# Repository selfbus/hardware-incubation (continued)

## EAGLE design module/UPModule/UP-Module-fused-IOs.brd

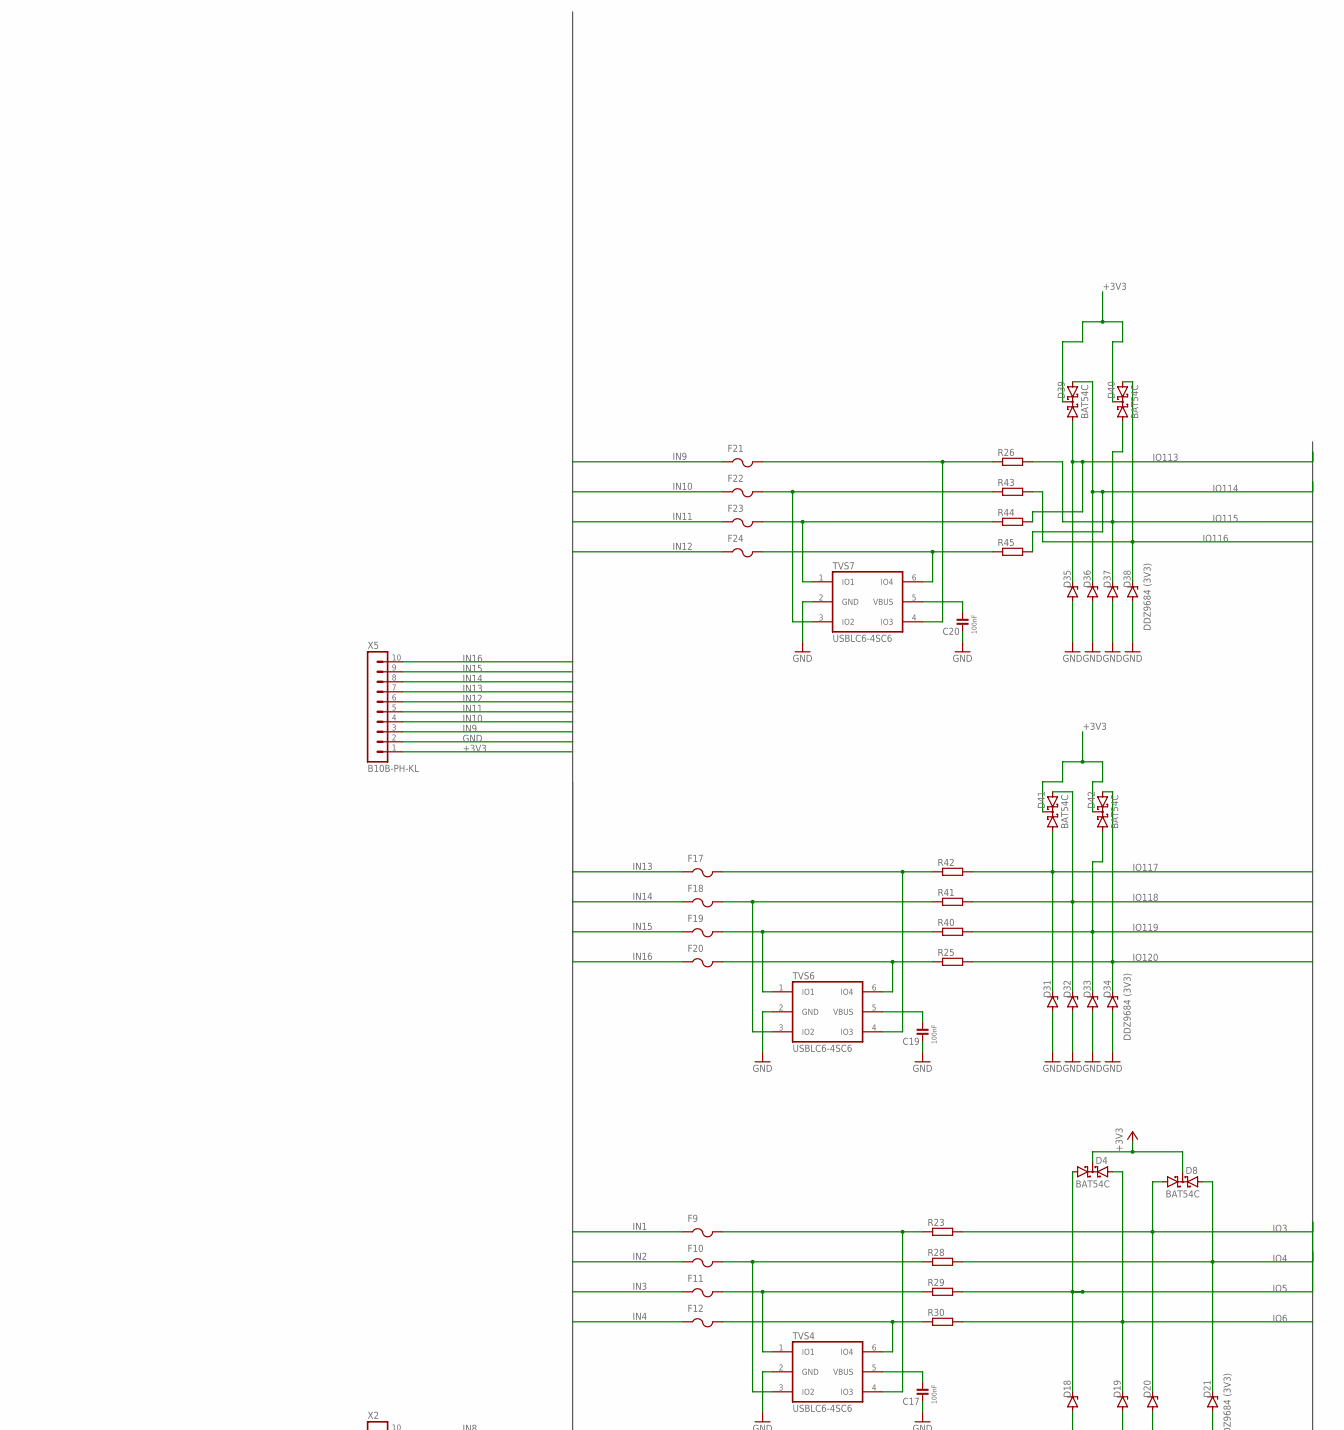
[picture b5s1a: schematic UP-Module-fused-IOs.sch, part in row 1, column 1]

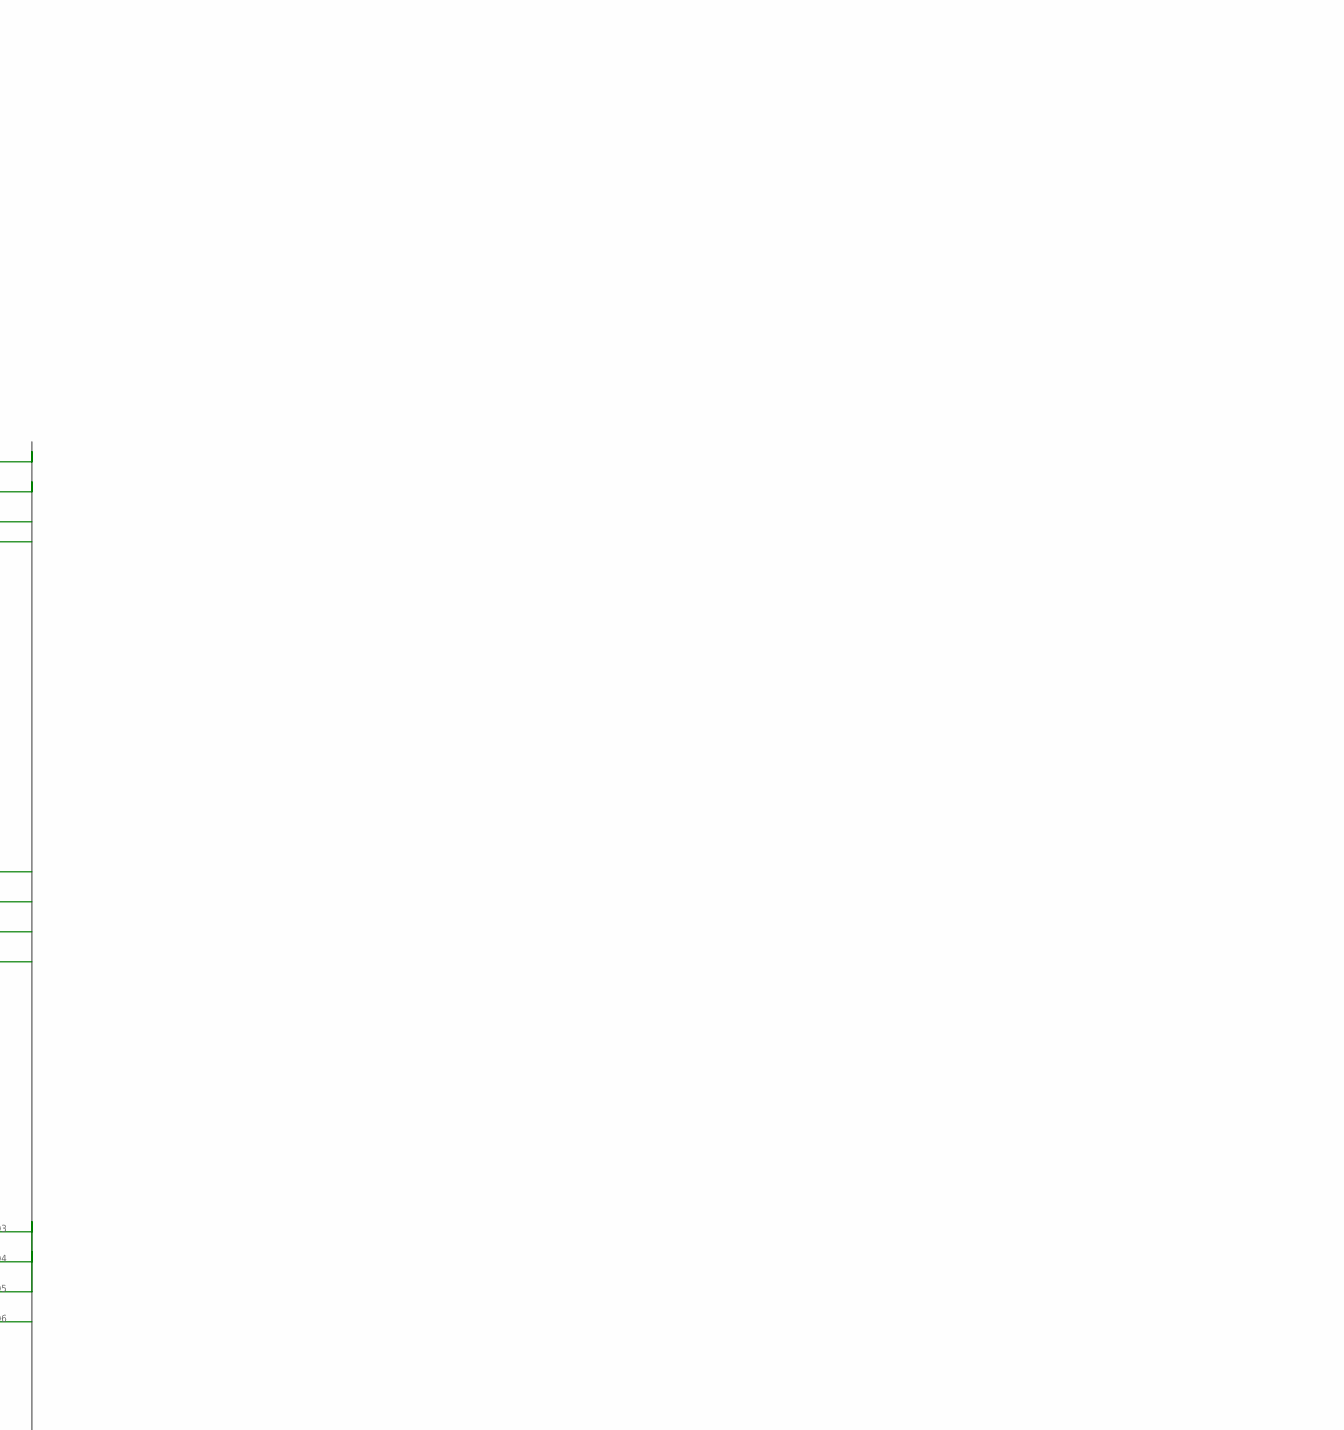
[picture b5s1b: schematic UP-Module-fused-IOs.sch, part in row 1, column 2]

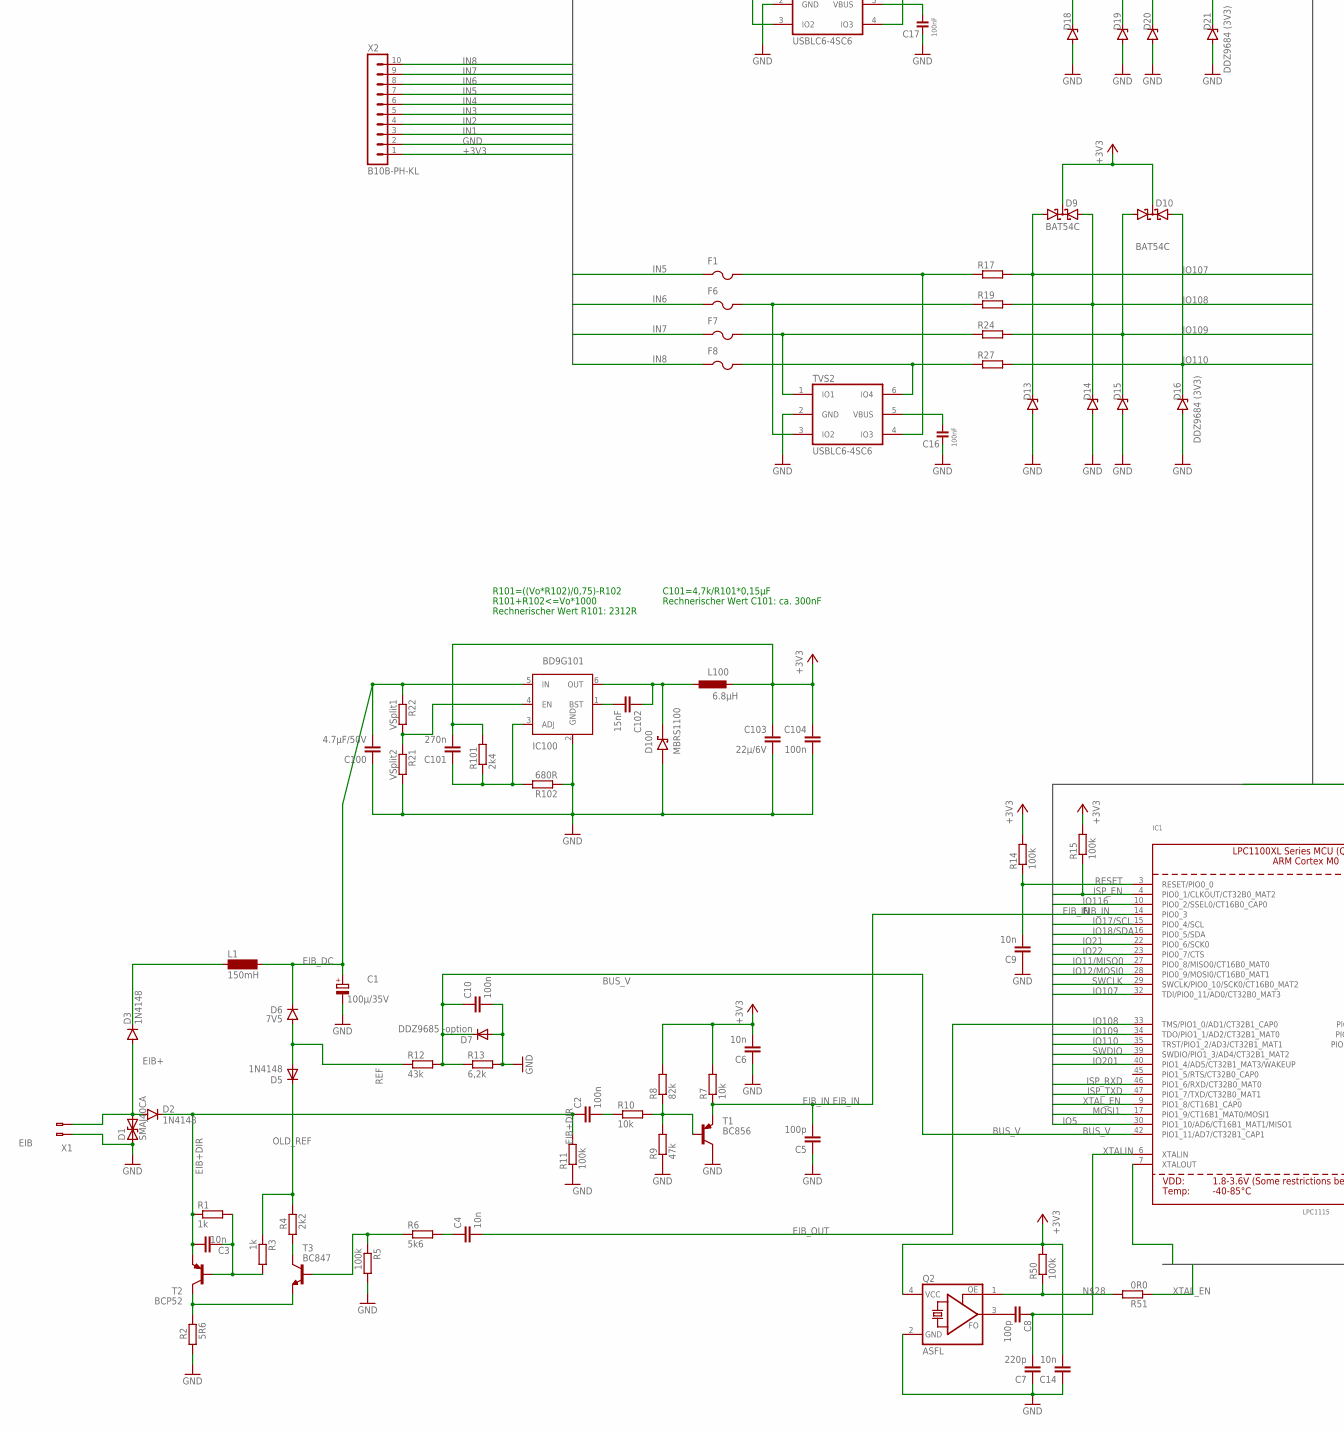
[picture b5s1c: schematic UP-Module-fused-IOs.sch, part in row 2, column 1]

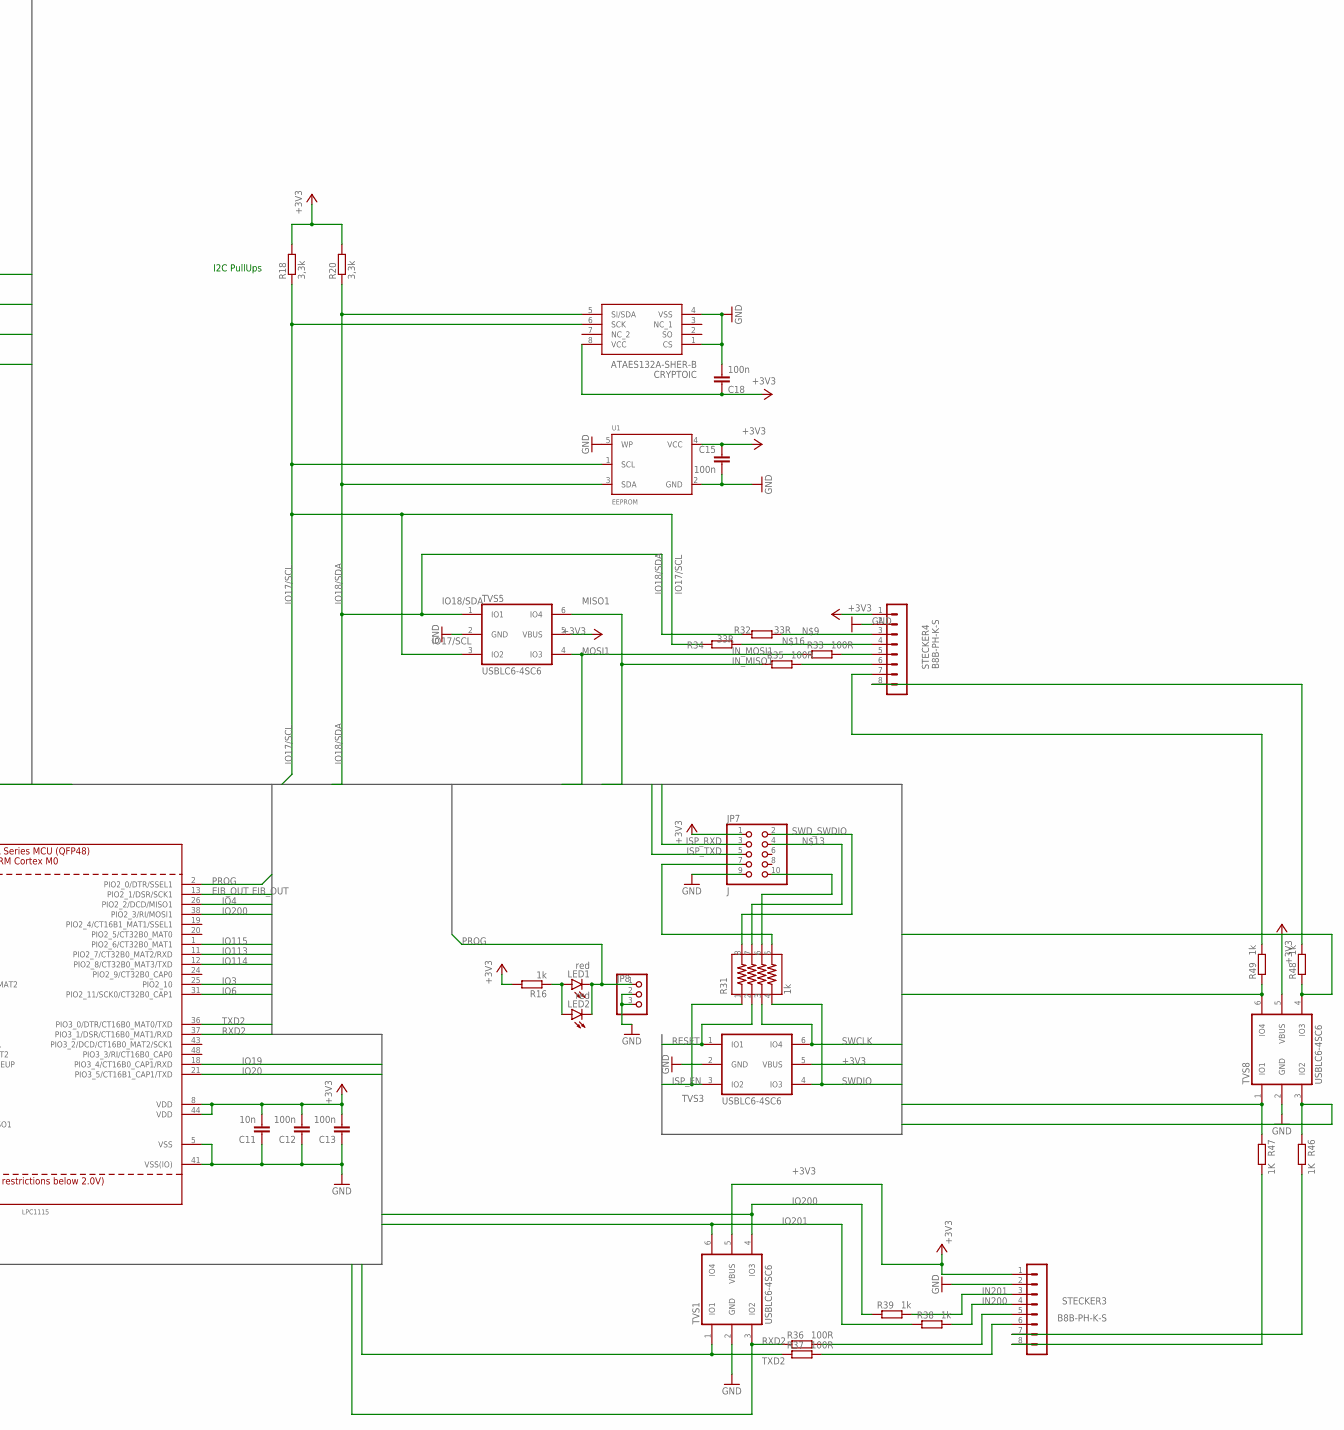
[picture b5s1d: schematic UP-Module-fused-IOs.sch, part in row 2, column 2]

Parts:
C1: 100µ/35V; SANYO-OSCON_SMD_C6
C2, C10, C12, C13, C15, C18, C104: 100n; C0805
C3, C4, C6, C9, C11, C14: 10n; C0805
C5, C8: 100p; C0805
C7: 220p; C0805
C16, C17, C19, C20: 100nF; C0805
C100: 4.7µF/50V; C0805
C101: 270n; C0805
C102: 15nF; C0805
C103: 22µ/6V; C0805
CRYPTOIC: ATAES132A-SHER-B; SOIC127P600X175-8N
D1: SMAJ40CA; DO214AC
D2, D3, D5: 1N4148; SOD323-R
D4, D8, D9, D10, D39, D40, D41, D42: BAT54C; SOT23
D6: 7V5; SOD323-R
D7: DDZ9685 -option; SOD-123
D13, D14, D15, D16, D18, D19, D20, D21, D31, D32, D33, D34, D35, D36, D37, D38: DDZ9684 (3V3); SODFL3718X115
D100: MBRS1100; SOD123FL
F1, F6, F7, F8, F9, F10, F11, F12, F17, F18, F19, F20, F21, F22, F23, F24: PTCFUSE-0805; F0805
IC1: LPC1115; LQFP48
IC100: BD9G101; SOT23-6
JP7: J; 2X05M
JP8: PINHD-1X3; 1X03
L1: 150mH; BS11
L100: 6.8µH; L4532P
LED1: red; CHIPLED_1206
LED2: red; LED3MM
Q2: ASFL; ASF
R1, R3, R16, R38, R39, R48, R49: 1k; R0805
R2: 5R6; R0805
R4: 2k2; R0805
R5, R11, R14, R15, R50: 100k; R0805
R6: 5k6; R0805
R7, R10: 10k; R0805
R8: 82k; R0805
R9: 47k; R0805
R12: 43k; R0805
R13: 6,2k; R0805
R17, R19, R23, R24, R25, R26, R27, R28, R29, R30, R40, R41, R42, R43, R44, R45: R-EU_R0805; R0805
R18, R20: 3,3k; R0805
R21: VSplit2; R0805
R22: VSplit1; R0805
R31: 1k; YC164-JR-0733RL
R32, R34: 33R; R0805
R33, R35, R36, R37: 100R; R0805
R46, R47: 1K; R0805
R51: 0R0; R0805
R101: 2k4; R0805
R102: 680R; R0805
STECKER3, STECKER4: B8B-PH-K-S
T1: BC856; SOT23-BEC
T2: BCP52; SOT223
T3: BC847; SOT23
TVS1, TVS2, TVS3, TVS4, TVS5, TVS6, TVS7, TVS8: USBLC6-4SC6; SOT-23-6L
U1: EEPROM; SOT23-5
X1: EIB; BUSKLEMME243-724
X2, X5: B10B-PH-KL; B10B-PH-K-S

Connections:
+3V3: C6.2, C11.2, C12.2, C13.2, C14.2, C15.1, C18.1, C101.2, C103.1, C104.1, CRYPTOIC.8 (VCC), D4.3 (CC), D8.3 (CC), D9.3 (CC), D10.3 (CC), D39.3 (CC), D40.3 (CC), D41.3 (CC), D42.3 (CC), IC1.8 (VDD), IC1.44 (VDD), JP7.1, L100.2, Q2.4 (VCC), R7.2, R8.2, R14.2, R15.2, R16.2, R18.2, R20.2, R50.2, R101.2, STECKER3.1, STECKER4.1, TVS1.5 (VBUS), TVS3.5 (VBUS), TVS5.5 (VBUS), TVS8.5 (VBUS), U1.4 (VCC), X2.1, X5.1
BST: C102.2, IC100.1 (BST)
BUS_V: C10.2, D7.C, IC1.42 (PIO1_11/AD7/CT32B1_CAP1), R12.2, R13.1
EIB+: D1.C (2), D2.A, D3.A, X1.2 (B-2)
EIB+DIR: C2.1, C3.1, D2.C, R1.1, R11.2, T2.3 (E)
EIB_DC: C1.+, C100.2, D6.C, IC100.5 (IN), L1.2, R22.1
EIB_IN: C5.2, IC1.14 (PIO0_3), R7.1, T1.E
EIB_OUT: C4.2, IC1.13 (PIO2_1/DSR/SCK1)
FB: C101.1, IC100.3 (ADJ), R101.1, R102.2
GND: C1.-, C5.1, C6.1, C7.1, C9.1, C10.1, C11.1, C12.1, C13.1, C14.1, C15.2, C16.1, C17.1, C18.2, C19.1, C20.1, C100.1, C103.2, C104.2, CRYPTOIC.1 (CS), CRYPTOIC.4 (VSS), D1.A (1), D7.A, D13.2 (A), D14.2 (A), D15.2 (A), D16.2 (A), D18.2 (A), D19.2 (A), D20.2 (A), D21.2 (A), D31.2 (A), D32.2 (A), D33.2 (A), D34.2 (A), D35.2 (A), D36.2 (A), D37.2 (A), D38.2 (A), D100.A, IC1.5 (VSS), IC1.41 (VSS(IO)), IC100.2 (GND), JP7.9, JP8.2, JP8.3, Q2.2 (GND), R2.1, R5.2, R9.1, R11.1, R13.2, R21.2, R102.1, STECKER3.2, STECKER4.2, T1.C, TVS1.2 (GND), TVS2.2 (GND), TVS3.2 (GND), TVS4.2 (GND), TVS5.2 (GND), TVS6.2 (GND), TVS7.2 (GND), TVS8.2 (GND), U1.2 (GND), U1.5 (WP), X1.1 (B-1), X2.2, X5.2
IN1: F9.1, X2.3
IN2: F10.1, X2.4
IN3: F11.1, X2.5
IN4: F12.1, X2.6
IN5: F1.1, X2.7
IN6: F6.1, X2.8
IN7: F7.1, X2.9
IN8: F8.1, X2.10
IN9: F21.1, X5.3
IN10: F22.1, X5.4
IN11: F23.1, X5.5
IN12: F24.1, X5.6
IN13: F17.1, X5.7
IN14: F18.1, X5.8
IN15: F19.1, X5.9
IN16: F20.1, X5.10
IN200: R38.2, STECKER3.4
IN201: R39.2, STECKER3.3
IN_MISO1: R35.2, STECKER4.6
IN_MOSI1: R33.2, STECKER4.5
IO3: D8.1 (A1), D20.1 (C), IC1.25 (PIO2_10), R23.2
IO4: D8.2 (A2), D21.1 (C), IC1.26 (PIO2_2/DCD/MISO1), R28.2
IO5: D4.1 (A1), D18.1 (C), IC1.30 (PIO1_10/AD6/CT16B1_MAT1/MISO1), R29.2
IO6: D4.2 (A2), D19.1 (C), IC1.31 (PIO2_11/SCK0/CT32B0_CAP1), R30.2
IO11/MISO0: IC1.27 (PIO0_8/MISO0/CT16B0_MAT0)
IO12/MOSI0: IC1.28 (PIO0_9/MOSI0/CT16B0_MAT1)
IO17/SCL: CRYPTOIC.6 (SCK), IC1.15 (PIO0_4/SCL), R18.1, R34.1, TVS5.3 (IO2), U1.1 (SCL)
IO18/SDA: CRYPTOIC.5 (SI/SDA), IC1.16 (PIO0_5/SDA), R20.1, R32.1, TVS5.1 (IO1), U1.3 (SDA)
IO19: IC1.18 (PIO3_4/CT16B0_CAP1/RXD), R47.1, TVS8.1 (IO1)
IO20: IC1.21 (PIO3_5/CT16B1_CAP1/TXD), R46.1, TVS8.3 (IO2)
IO21: IC1.22 (PIO0_6/SCK0), R49.1, TVS8.6 (IO4)
IO22: IC1.23 (PIO0_7/CTS), R48.1, TVS8.4 (IO3)
IO107: D9.1 (A1), D13.1 (C), IC1.32 (TDI/PIO0_11/AD0/CT32B0_MAT3), R17.2
IO108: D9.2 (A2), D14.1 (C), IC1.33 (TMS/PIO1_0/AD1/CT32B1_CAP0), R19.2
IO109: D10.1 (A1), D15.1 (C), IC1.34 (TDO/PIO1_1/AD2/CT32B1_MAT0), R24.2
IO110: D10.2 (A2), D16.1 (C), IC1.35 (TRST/PIO1_2/AD3/CT32B1_MAT1), R27.2
IO113: D35.1 (C), D39.1 (A1), IC1.11 (PIO2_7/CT32B0_MAT2/RXD), R44.2
IO114: D36.1 (C), D39.2 (A2), IC1.12 (PIO2_8/CT32B0_MAT3/TXD), R45.2
IO115: D37.1 (C), D40.1 (A1), IC1.1 (PIO2_6/CT32B0_MAT1), R26.2
IO116: D38.1 (C), D40.2 (A2), IC1.10 (PIO0_2/SSEL0/CT16B0_CAP0), R43.2
IO117: D31.1 (C), D41.1 (A1), R42.2
IO118: D32.1 (C), D41.2 (A2), R41.2
IO119: D33.1 (C), D42.1 (A1), R40.2
IO120: D34.1 (C), D42.2 (A2), R25.2
IO200: IC1.38 (PIO2_3/RI/MOSI1), R39.1, TVS1.4 (IO3)
IO201: IC1.40 (PIO1_4/AD5/CT32B1_MAT3/WAKEUP), R38.1, TVS1.6 (IO4)
ISP_EN: IC1.4 (PIO0_1/CLKOUT/CT32B0_MAT2), R15.1, R31.1, TVS3.3 (IO2)
ISP_RXD: IC1.46 (PIO1_6/RXD/CT32B0_MAT0), JP7.3
ISP_TXD: IC1.47 (PIO1_7/TXD/CT32B0_MAT1), JP7.5
LX: C102.1, D100.C, IC100.6 (OUT), L100.1
MISO1: R35.1, TVS5.6 (IO4)
MOSI1: IC1.17 (PIO1_9/CT16B1_MAT0/MOSI1), R33.1, TVS5.4 (IO3)
unnamed: C2.2, R10.1
unnamed: D3.C, L1.1
unnamed: C4.1, R6.2
unnamed: IC100.4 (EN), R21.1, R22.2
unnamed: R4.1, T3.3 (C)
unnamed: R2.2, T2.2 (C), T2.4 (C), T3.2 (E)
unnamed: JP7.7, R31.5
unnamed: R32.2, STECKER4.3
unnamed: C8.2, Q2.3 (FO)
unnamed: JP7.10, R31.6
unnamed: R5.1, R6.1, T3.1 (B)
unnamed: JP7.4, R31.7
unnamed: R8.1, R9.2, R10.2, T1.B
unnamed: C3.2, R1.2, R3.2, T2.1 (B)
unnamed: R34.2, STECKER4.4
unnamed: F1.2, R17.1, TVS2.4 (IO3)
unnamed: F6.2, R19.1, TVS2.3 (IO2)
unnamed: F7.2, R24.1, TVS2.1 (IO1)
unnamed: F8.2, R27.1, TVS2.6 (IO4)
unnamed: C16.2, TVS2.5 (VBUS)
unnamed: F10.2, R28.1, TVS4.3 (IO2)
unnamed: F12.2, R30.1, TVS4.6 (IO4)
unnamed: C17.2, TVS4.5 (VBUS)
unnamed: F11.2, R29.1, TVS4.1 (IO1)
unnamed: F9.2, R23.1, TVS4.4 (IO3)
unnamed: Q2.1 (OE), R50.1, R51.2
unnamed: R36.2, STECKER3.5
unnamed: R37.2, STECKER3.6
unnamed: F18.2, R41.1, TVS6.3 (IO2)
unnamed: F20.2, R25.1, TVS6.6 (IO4)
unnamed: C19.2, TVS6.5 (VBUS)
unnamed: F19.2, R40.1, TVS6.1 (IO1)
unnamed: F17.2, R42.1, TVS6.4 (IO3)
unnamed: F22.2, R43.1, TVS7.3 (IO2)
unnamed: F24.2, R45.1, TVS7.6 (IO4)
unnamed: C20.2, TVS7.5 (VBUS)
unnamed: LED1.A, LED2.A, R16.1
unnamed: F23.2, R44.1, TVS7.1 (IO1)
unnamed: F21.2, R26.1, TVS7.4 (IO3)
unnamed: R47.2, STECKER3.8
unnamed: R46.2, STECKER3.7
unnamed: R49.2, STECKER4.7
unnamed: R48.2, STECKER4.8
OLD_REF: D5.C, R3.1, R4.2
PROG: IC1.2 (PIO2_0/DTR/SSEL1), JP8.1, LED1.C, LED2.K (C)
REF: D5.A, D6.A, R12.1
RESET: C9.2, IC1.3 (RESET/PIO0_0), R14.1, R31.2, TVS3.1 (IO1)
RXD2: IC1.37 (PIO3_1/DSR/CT16B0_MAT1/RXD), R36.1, TVS1.3 (IO2)
SWCLK: IC1.29 (SWCLK/PIO0_10/SCK0/CT16B0_MAT2), R31.3, TVS3.6 (IO4)
SWDIO: IC1.39 (SWDIO/PIO1_3/AD4/CT32B1_MAT2), R31.4, TVS3.4 (IO3)
SWD_SWDIO: JP7.2, R31.8
TXD2: IC1.36 (PIO3_0/DTR/CT16B0_MAT0/TXD), R37.1, TVS1.1 (IO1)
XTALIN: C7.2, C8.1, IC1.6 (XTALIN)
XTALOUT: IC1.7 (XTALOUT)
XTAL_EN: IC1.9 (PIO1_8/CT16B1_CAP0), R51.1

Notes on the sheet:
R101=((Vo*R102)/0,75)-R102
R101+R102<=Vo*1000
Rechnerischer Wert R101: 2312R
C101=4,7k/R101*0,15µF
Rechnerischer Wert C101: ca. 300nF
I2C PullUps

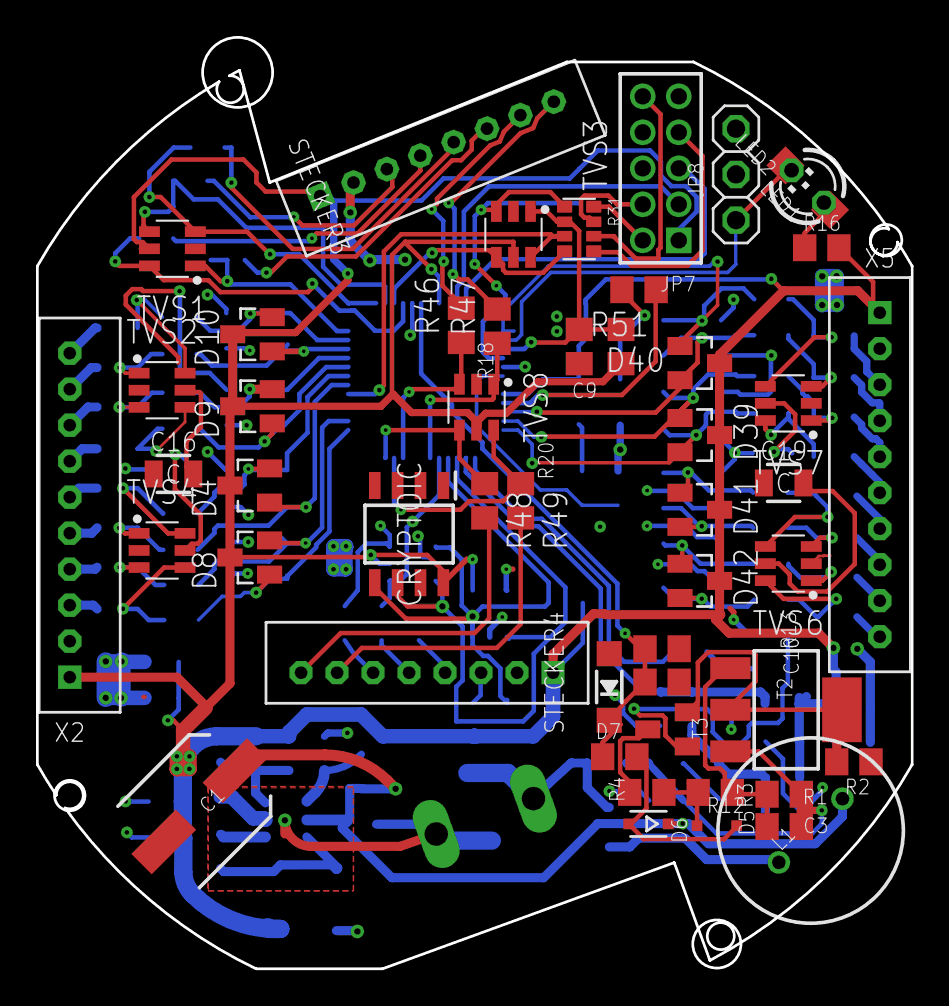
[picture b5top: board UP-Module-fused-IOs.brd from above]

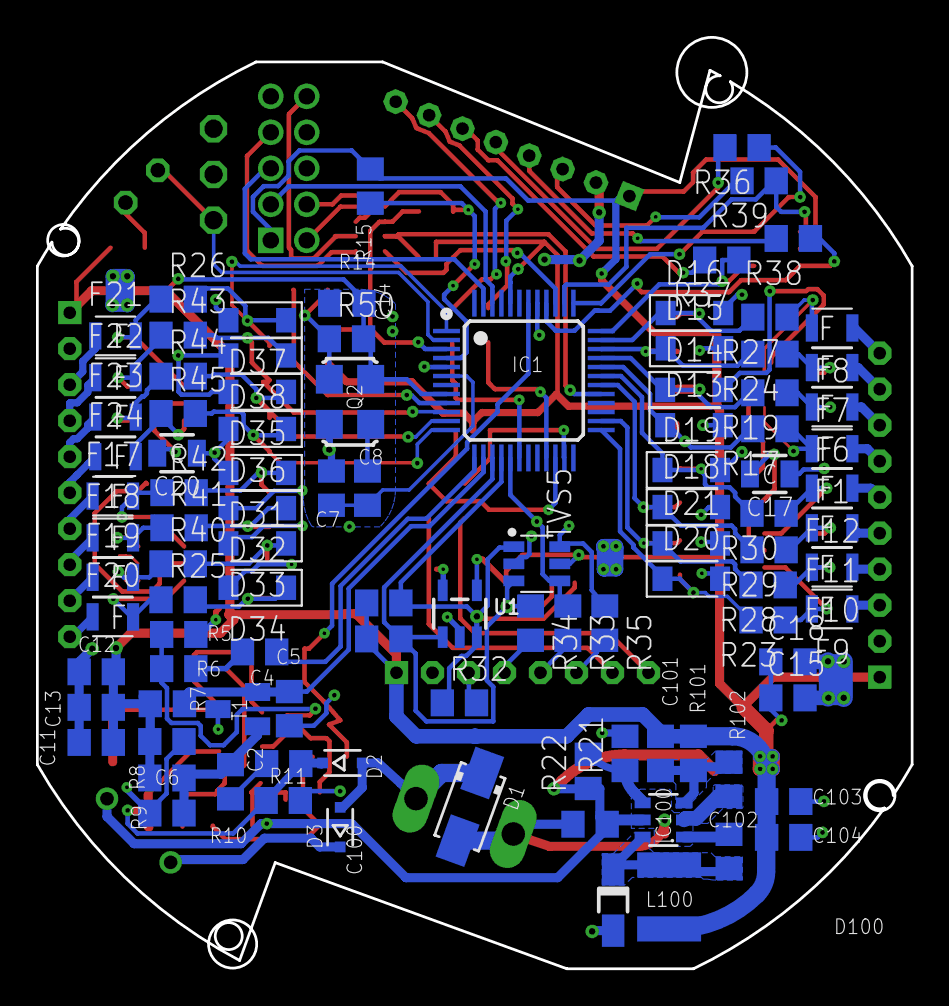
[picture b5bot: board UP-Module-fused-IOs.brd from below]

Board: 2 copper layers, 48.6 x 51.7 mm, 152 parts (101 on the bottom side), 114 nets.

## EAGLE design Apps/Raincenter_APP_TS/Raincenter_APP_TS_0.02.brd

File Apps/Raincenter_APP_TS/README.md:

# Raincenter_APP_TS

KNX-Modul für das Hauswasserwerk ESPA-Tacomat bzw. Raincenter Comfort 15
KNX-module for the domestic waterworks ESPA-Tacomat or Raincenter Comfort 15

[Firmware: raincenter-bim112](https://github.com/selfbus/software-arm-incubation/tree/master/sensors/misc/raincenter-bim112)

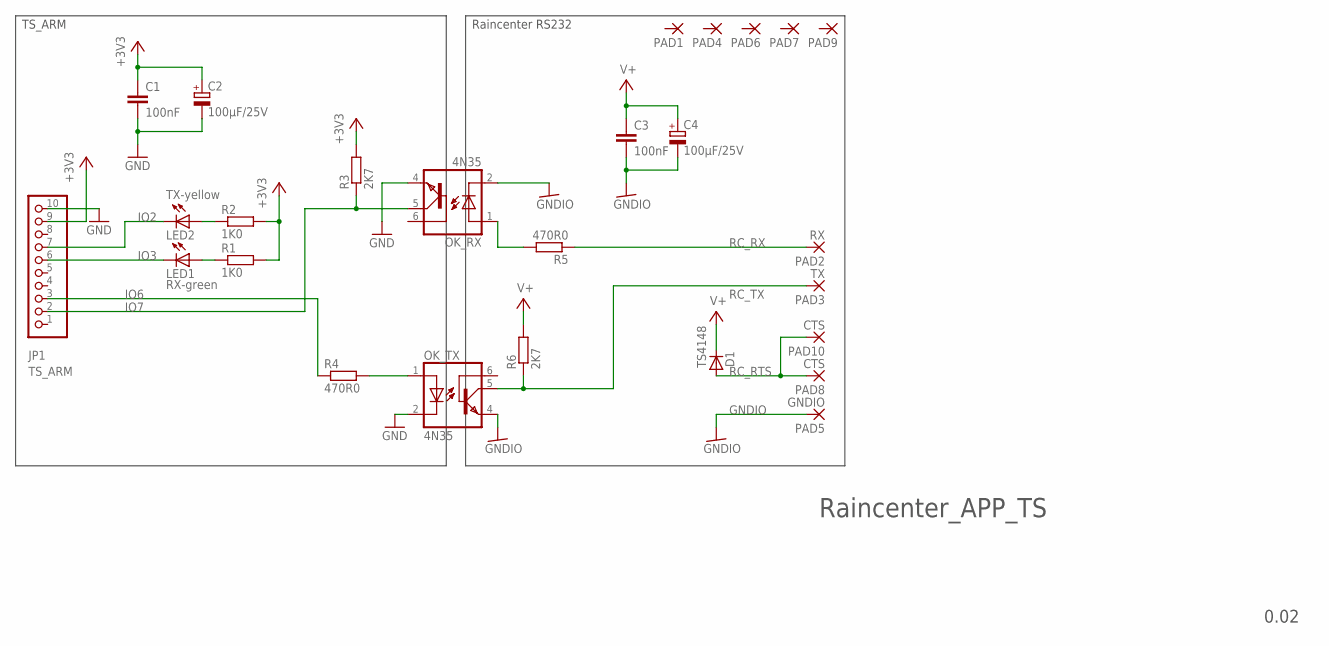
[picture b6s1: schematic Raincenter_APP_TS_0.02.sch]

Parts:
C1, C3: 100nF; C1206K
C2, C4: 100µF/25V; PANASONIC_D
D1: TS4148; 1206
JP1: TS_ARM; 1X10
LED1: RX-green; CHIPLED_1206
LED2: TX-yellow; CHIPLED_1206
OK_RX: 4N35; DIL06
OK_TX: 4N35; DIL06
PAD1, PAD4, PAD6, PAD7, PAD9: WIREPADSMD1,27-254; SMD1,27-2,54
PAD2: RX; SMD1,27-2,54
PAD3: TX; SMD1,27-2,54
PAD5: GNDIO; SMD1,27-2,54
PAD8, PAD10: CTS; SMD1,27-2,54
R1, R2: 1K0; R1206
R3, R6: 2K7; R1206
R4, R5: 470R0; R1206

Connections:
+3V3: C1.1, C2.+, JP1.9, R1.2, R2.2, R3.2
GND: C1.2, C2.-, JP1.10, OK_RX.4 (EMI), OK_TX.2 (C)
GNDIO: C3.2, C4.-, OK_RX.2 (C), OK_TX.4 (EMI), PAD5.1
IO2: JP1.7, LED2.C
IO3: JP1.6, LED1.C
IO6: JP1.3, R4.1
IO7: JP1.2, OK_RX.5 (COL), R3.1
unnamed: LED2.A, R2.1
unnamed: OK_RX.1 (A), R5.2
unnamed: OK_TX.1 (A), R4.2
unnamed: LED1.A, R1.1
RC_RTS: D1.ANODE (A), PAD8.1, PAD10.1
RC_RX: PAD2.1, R5.1
RC_TX: OK_TX.5 (COL), PAD3.1, R6.1
V+: C3.1, C4.+, D1.KATHODE (K), R6.2

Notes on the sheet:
Raincenter_APP_TS
0.02
Raincenter RS232
TS_ARM

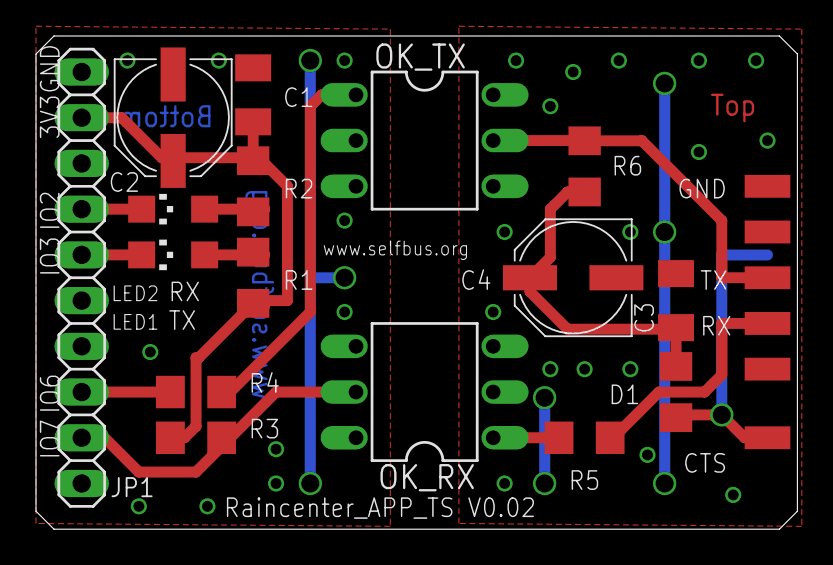
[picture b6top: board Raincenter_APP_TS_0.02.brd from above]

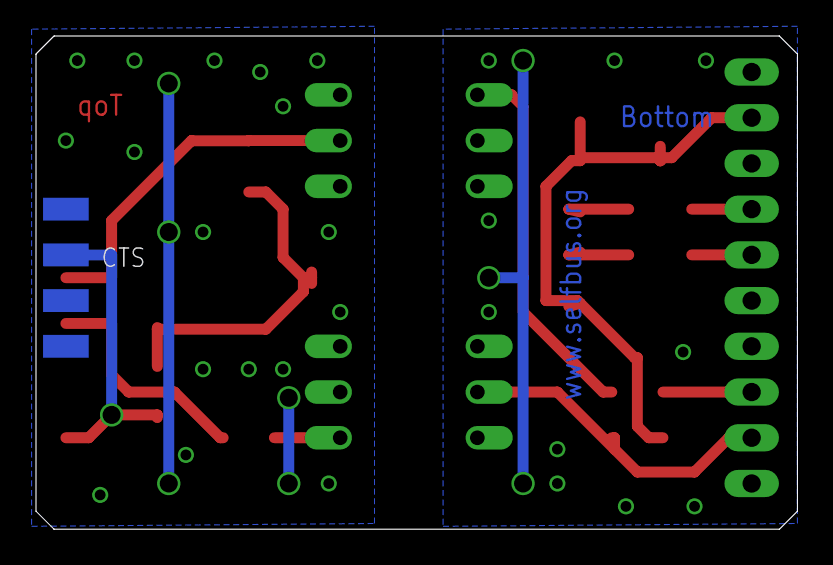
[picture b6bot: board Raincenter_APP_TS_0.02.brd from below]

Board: 2 copper layers, 42.3 x 27.4 mm, 26 parts (4 on the bottom side), 15 nets.

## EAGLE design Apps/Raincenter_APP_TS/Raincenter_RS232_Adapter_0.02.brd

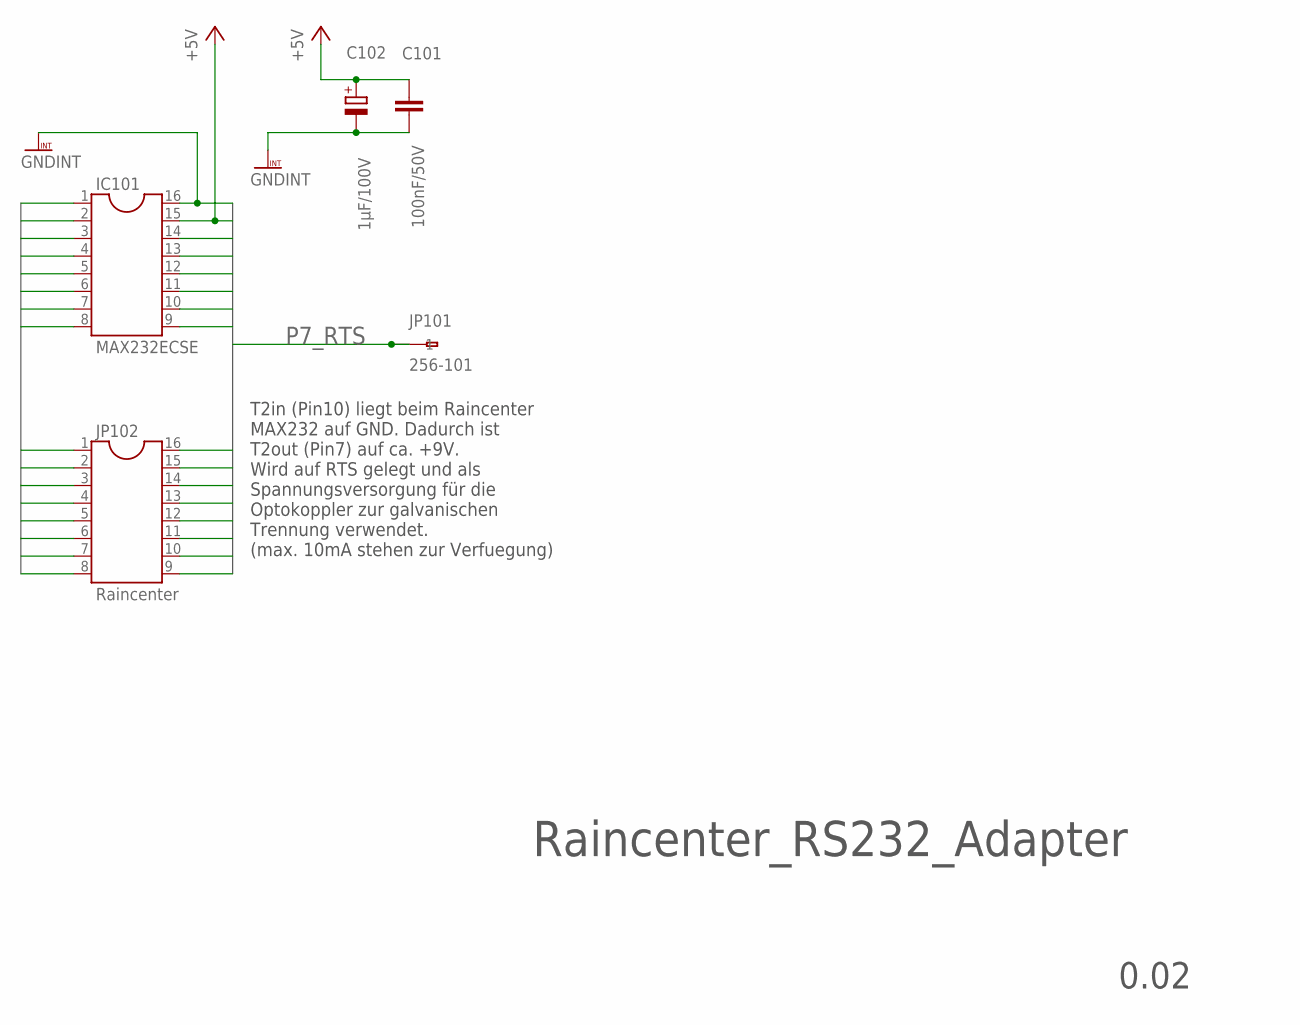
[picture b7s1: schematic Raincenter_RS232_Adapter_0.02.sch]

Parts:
C101: 100nF/50V; C025-024X044
C102: 1µF/100V; E2,5-6
IC101: MAX232ECSE; SOCKET-16
JP101: 256-101; 255-401-5
JP102: Raincenter; SOCKET-16; MPN AR-16-ST/T

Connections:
+5V: C101.1, C102.+, IC101.15, JP102.2
GNDINT: C101.2, C102.-, IC101.16, JP102.1
P1: IC101.1, JP102.16
P2: IC101.2, JP102.15
P3: IC101.3, JP102.14
P4: IC101.4, JP102.13
P5: IC101.5, JP102.12
P6: IC101.6, JP102.11
P7_RTS: IC101.7, JP101.A1 (1), JP101.B1 (2), JP102.10
P8: IC101.8, JP102.9
P9: IC101.9, JP102.8
P10: IC101.10, JP102.7
P11: IC101.11, JP102.6
P12: IC101.12, JP102.5
P13: IC101.13, JP102.4
P14: IC101.14, JP102.3

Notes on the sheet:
Raincenter_RS232_Adapter
0.02
T2in (Pin10) liegt beim Raincenter MAX232 auf GND. Dadurch ist T2out (Pin7) auf ca. +9V. Wird auf RTS gelegt und als Spannungsversorgung für die Optokoppler zur galvanischen Trennung verwendet. (max. 10mA stehen zur Verfuegung)

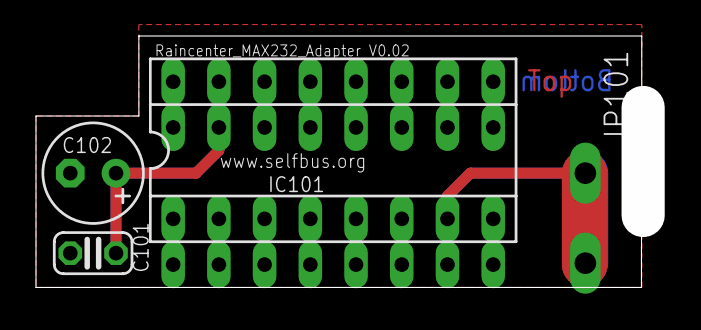
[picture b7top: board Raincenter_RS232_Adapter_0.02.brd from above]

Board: 2 copper layers, 33.7 x 14.0 mm, 5 parts (1 on the bottom side), 16 nets.

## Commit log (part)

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2012-11-26 first upload
2013-01-06 first upload new version 4.3
2013-01-06 first upgrate to new basic circuit
2013-01-09 first upload SB_TS
2013-01-13 neue Versionen TS DIL zugefügt
2013-01-29 prototype Version, vorsicht änderung am osc
2013-01-30 Falsche Anmerkung entfernt
2013-02-10 Text entfernt/ geändert Signed-off-by: oldcoolman <service@krieger-elektro.de>
2013-02-19 first upload TS DIL
2013-02-21 RM2.0 first upload
2013-02-21 pinbelegung zugefügt
2013-02-21 Steckerbelegung um RXD und TXD erweitert Verzeichnis umbenannt auf "App-Controller Steckerbelegung"
2013-02-21 Verzeichnis umbenannt
2013-02-22 Pin Vext auf Versorgung korrigiert
2013-02-27 Alte Schaltungen entfernt
2013-03-01 Falsche Dateien entfernt, LED Taster besser benannt
2013-03-02 first revision Signed-off-by: oldcoolman <service@krieger-elektro.de>
2013-03-08 Umbauanleitung 1.3 auf 2.0
2013-03-15 add eagle files from raspberry pi controller version 1.0
2013-03-15 RPI Bus Controller: Prototyp entfernt, neue Version ins richtige Verzeichnis geschoben
2013-03-16 Creation of Eagle Libraries directory and add hammond boxes size
2013-03-25 Korrektur Verbindung 13->11, Dank an Tontechniker für die Meldung.
2013-03-28 CHG: CAP Package changed to 1206
2013-03-28 CHG wire angle fixed
2013-04-01 first upload Signed-off-by: oldcoolman <service@krieger-elektro.de>
2013-04-05 Taster Small Box V1
2013-04-06 SmallBox Change corrupt files
2013-04-06 New position for capacitor near to oscillator
2013-04-10 Rauchmelder Umbau auf Version 2.1
2013-05-07 upload usb progger
2013-05-11 Update der Rauchmelder Workarounds
2013-05-15 first upload usb modular
2013-05-19 first na du weisst schon...
2013-05-19 Dimmer V1.3 erstellt aus Dimmer V1 mit Workaround 3
2013-05-25 Gitignore for Eagle temp files, added missing C to dimmer workaround
2013-05-25 Updated the README and gitignore
2013-05-25 Torsteuerung initial upload
2013-05-25 Moved lpc922_4te to hardware repository, Renamed controller top-level directory to Controller, Moved 4te controller sub projects directly into Controller
2013-05-26 deleted
2013-06-07 Audioaktor: ICs beschriftet
2013-06-08 Rauchmelder verschoben nach hardware
2013-07-07 new 2TE Versions
2013-10-11 first upload oldi
2013-10-11 Tasterschnittstelle_DIL übersiedelte nach UPModule
2013-10-11 version 2.53 gelöscht und kerkobug 10nF am OSC von 1.54 gefixt.
2013-10-11 Zwischenversionen entfernt
2013-11-11 Regenmesser nach Apps verschoben.
2013-11-22 add a new version of top controller. the most part now one ONE side.
2013-12-14 modifiziert
2013-12-14 nochmal..
2014-01-17 Gira Tastsensor 3 CAD LibreCad
2014-01-21 aktualisierte .dxf des TS3
2014-01-21 aktualisierte DXF
2014-01-21 TS3 DXF Korrekturen
2014-02-03 2TE controller
2014-04-06 Entwurf ARM Controller 4TE
2014-04-06 Final V0.08
2014-04-06 Open questions added
2014-04-07 Exchange PWM and LT9
    To support a LPC11Uxx device and have the two pins required for the USB on
    the LED/Taster pinhead the old PWM and LT9 have been swaped.
2014-04-07 Additional GND added to App pinheader
    On pin 21 a new GND has been added. The following pins have been rearraged
    to keep all ADV channels.
2014-04-07 Improoved GND plane on BOT
2014-04-08 small changes
2014-04-08 C near Osci moved
2014-04-08 Beschriftungen aufgeräumt
    neue Datei: ARM-LPC1115_V0.10.brd
    neue Datei: ARM-LPC1115_V0.10.sch
2014-04-08 Small layout changes
2014-04-08 Version text on PCB changed
2014-05-17 duko gnd ergänzt, anschluss smcc
2014-05-24 LPC1115 SMD - Cleanup routing - Crystal and LEDs added
2014-05-25 LPC1115 SMD - 10nF X7R wie auf LPC Expressor Board hinzugefügt - Elko auf 3V3 Seite für Applikation mit erhöhtem Strombedarf hinzugefügt - 2 LEDs auf dem ARM Board hinzugefügt - Cleanup
2014-06-04 LPC1115 SMD: added GND VIAs
2014-06-04 LPC1115 SMD: Done! V1.0 RC 1 - TVS, Power Led hinzugefügt
2014-06-12 Labels angepasst, VSEL Pinhead update und umbenannt
2014-06-13 Bezeichungen verschoben und Hinweise ergänzt
2014-06-15 D2 bei Busspannungs-AD durch C ersetzt
2014-06-15 LPC1115 SMD: Low-Pass filter for ADC reading, silkscreen fixed
2014-06-15 ARM Controller Cleanup, ARM LCD+Taster
    - ARM Controller Verzeichnis aufgeräumt, letzte Version v1.0 genannt
    - ARM LCD+Taster Entwurf eingecheckt
2014-09-29 Added LPC compatibility pin information
2014-09-29 Update LPC compatibility pin information, LPC-Link cable added
2014-12-15 LPC922-DIL-SMD Adapter
2015-03-15 all components rearranged added programming interface with rm 2.54 (compatible with USB programmer) added TXD solder bridge preparation for horizontal WAGO
2015-04-28 New Version for RPi B+ and RPi 2B
2015-05-15 first upload TS-ARM3.05
2015-07-01 LPC-Link JP4
2015-10-07 current limiter for transmitter, change prog led behaviour, fix clamp layout
2015-11-20 fix receiver voltage protection
2015-12-21 umbau auf crystal, welches jedoch noch zu klein ist!
2016-01-12 HAT für FT12 einseitig bestückt
2016-01-16 TXD RXD getauscht
2016-01-17 Quarz footprint auf ASF geändert
2016-01-17 drc debug
2016-01-21 Schutzwiderstände in TXD_ARM und EIB-OUT_ARM eingefügt
2016-01-24 Beschriftung Ver/GND im Schaltplan berichtigt.
2016-01-25 Reduce VIAs, connect GND areas
2016-01-26 Fixed last commit
2016-02-07 Add TX/RX resistors and decoupling capacitors for ADUM.
2016-02-14 Raspi HAT Dual MCU - rerouted
2016-02-15 BUS-ADC zugefügt
2016-02-19 OSC mit C-teiler
2016-02-20 2TE controller mit OSC und C-Teiler
2016-02-22 VCC Leiche beim progtaster entfernt
2016-03-19 c Teiler beim OSC zugefügtV1.01
2016-03-19 LCD Taster PCB geroutet
2016-03-22 kosmetik
2016-03-29 Referenz vias zugefügt.
2016-03-31 stoplackflaeche im via pin3 OSC zugefuegt
2016-04-03 value cap divider changed, micro vias with tstop, and hole free on top
2016-04-03 cap dividor value changed
2016-04-04 Referenzvias zugefuegt.
2016-04-04 GND Vias, Silkscreen, etc. auf MCU Seite
2016-04-09 Finalize Raspi HAT Dual MCU board
2016-04-19 gnd via drill to 0.3mm, place separate bstop over this drills
2016-04-19 Kosmetik am 2TE ARM
2016-06-05 R Teiler für APP ID zugefügt
2016-06-12 Id-resistor package changed to 1206 and replace.
2016-06-12 Rauchmelder mit ARM 3.0
2016-06-12 Beschriftungen geändert
2016-10-20 pass via in cream mask deleted.
2016-10-23 runde cream entfernt
2016-12-11 IO / spi modify
2017-03-06 Added schematics and layouts for the 6x current-sensing switch module.
2017-04-14 Taster ARM erste Vorschlaege des Anschlusses am ARM.
2017-04-15 naechster Vorschlag
2017-04-16 vorschlag Erweiterungsstecker
2017-04-18 weiter geroutet...
2017-04-30 weiss nicht mehr...
2017-05-07 Paar Pauteile und vias verschoben
2017-05-09 Überwachung der Bodenplatte hinzugefügt + Beschriftung auf Platine verändert (Names layer)
    Die Überwachung, ob der Rauchmelder auf der Bodenplatte gesteckt und
    somit aktiv ist, wird über die interne Spannung des Rauchmelders
    erledigt. Diese ist an Pin 11+12 der Schnittstelle zu finden.
2017-07-21 WIP: Redesigning RM ARM PCB power supply and clock
2017-08-05 WIP: RM ARM routing done. Need to check ground VIAs and silk screen
2017-09-03 Update App out6_cs, update Controller lpc1115_4te_top
2017-09-03 Forgot to add the CAM project files...
2017-10-12 R29 auf out6_cs-ctrl V1.1 auf unbestückt geändert
2017-11-15 silkscreen tvalue not printing on brd
2018-03-22 DRC error beseitigt
2018-04-06 D100 insert with footprint sma
2018-04-08 aenderungen R12 C101, JP1
2018-04-08 overlap beseitigt
2018-04-09 Taster nach rechts geschoben
2018-04-11 Initial commit of RasPI-TPUART
2018-04-11 Revert "Initial commit of RasPI-TPUART"
    This reverts commit 3a7352cee3a7ec6d12a70a96cf5c11f9496d37f9.
2018-04-14 Add rx and tx led. Optional. Bridge the led pads, if no need.
2018-04-27 Unrouted error behoben
2018-07-16 Added Rauchmelder_3.6:
    - All parts are places on the top side (except for the long pin header,
    of course).
    - Gerber files for individual PCBs and for a 2-PCB panel with fiducials
    for pick-and-place.
    - Source files are in KiCAD-5.0 format
2018-07-16 Fix a few part values in Rauchmelder_3.5
2018-10-09 USB-Interface ARM hinzugefügt
2019-10-21 first official upload
2019-10-26 upload CNC data
2019-10-29 Connected PIN13 to ARM
    But see discussion here: https://selfbus.forums3.com/post4309.html#p4309
2020-01-09 KNX Steckklemmenblock initialer Upload
    3D-Druck Dateien zum Herstellen einer Halterung für Lötstifte, um mit einer KNX Steckklemme REG Geräte anzuschließen.
2020-03-15 2out_16A_bi_TS-ARM_V1.0 added
2020-03-15 neu: 2out-Gehäuse
2020-03-16 neu: Isoplatte für 2out-Gehäuse
2020-03-29 Spannungsteiler auf 91k/10k geändert
2021-02-16 V1.1 (ISP UART Header added)
2021-02-24 UART Header Label added
2021-05-02 Raincenter_APP_TS: first initial commit, KNX-module for the domestic waterworks ESPA-Tacomat or Raincenter Comfort 15
2021-05-02 New UP Module with fused IOs
    Initial commit of new in wall module with as many IOs as possible. New PCB size for solid walls and dry construction.
    Work in progress.
2021-09-07 Update of UP Module with fused IOs
    Completely changed how IOs will be protected. EEPROM and cropty IC added.
2021-11-05 UP Module with fused IOs: alpha version
    routing of a version with max. IOs / functions fitting on a single PCB for in-wall installation done. Parts size 0805.
2022-01-31 Schematic as PDF and Interactive BOM added.
2022-02-15 RPi-TPUART: Edited font sizes and tantalum markers
    Catching up on missing push from 2019.
2022-05-19 [LPC1115_4TE_TOP] added iBOM and eagle project
2022-05-19 [out6_cs] added iBOM and eagle project
2022-11-08 Anpassungen BOM out6_cs
2022-11-14 [2out_16A] added interactive BOM's
2022-11-30 [Raspi-TPUART] added interactive BOM
2023-01-22 [RM] - added buck enable voltage divider
    as discussed via chat the voltage divider values were set
    new parts for bus voltage detection added
2023-01-22 [RM] - optimized capacitors for ARM and routing
    2 x 1µF and 100nF were placed near ARM as well as 100pF in EIB_IN line to eliminate spikes
2023-01-22 [RM] - added second (optional) 22µF to optimize power supply
    --> ripple is further flattened
2023-01-22 [RM] - removed voltage divider again, added status LEDs, ...
    - after a long discussion: we should use nowhere the voltage divider!
    - status LEDs will help to identify problems when building the module
    - optimized schematic
    - added fiducials
    - changed D1 to SMA footprint again
2023-01-25 [RM] Addition of power supply switch
    The power supply has to be shut off before connecting the RM to the base plate. A few part are necessary to get this function on the board.
2023-01-25 [RM] Routed pwr suply switch / base detection
    Merged olterions change with most recent verison
    Routed addtional parts for base detection and pwr supply switch
    Removed accidentially added v3.8.3
2023-01-26 [RPi-HAT...] interactive BOM for v0.8, v0.9b, v0.9c
2023-01-26 [RM] - pwr mlccs changed to 2 x 47uF and adj-voltage divider 1k6/470R
    - according to ROHM spec: switched to 2 x 47uF mlccs (instead of 1 x 22uF of the old design)
    - according to ROHM spec: adjusted voltage divider to get 3,3V output instead of (instead of 3,397V from the old design)
2023-01-27 [RM] - removed thermals from buck converter polygons
2023-01-27 [RM] - changed footprints from 1206 to 0805
2023-01-28 [RM] - removed vendor attributes from parts
    attributes were not updated and thus were misleading because auf wrong c&p values. So it's better to delete them completely (and perhaps add a dedicated BOM later)
2023-01-29 [RM] - optimized silkscreen
2023-02-08 [RM] - changed values to standard values
2023-03-22 [RM] - rearranged diodes; added holes for pull out zip tie
2023-03-25 [RM] - corrected some small bugs
    corrected directions of status LEDs
    changed C102 1206 -> 0805
    changed L1 6.8uH -> 4.7uH
    changed C101 270 -> 470nF
2023-03-26 [RM] - corrected some small bugs - 2nd try
    something went wrong yesterday - now again:
    corrected directions of status LEDs
    changed C102 1206 -> 0805
    changed L1 6.8uH -> 4.7uH
    changed C101 270 -> 470nF
2023-04-19 [SB-TS] - deleted SB_TS (lpc922) board which was never finalised
2023-04-19 [TS-ARM] - new version TS ARM 3.09
